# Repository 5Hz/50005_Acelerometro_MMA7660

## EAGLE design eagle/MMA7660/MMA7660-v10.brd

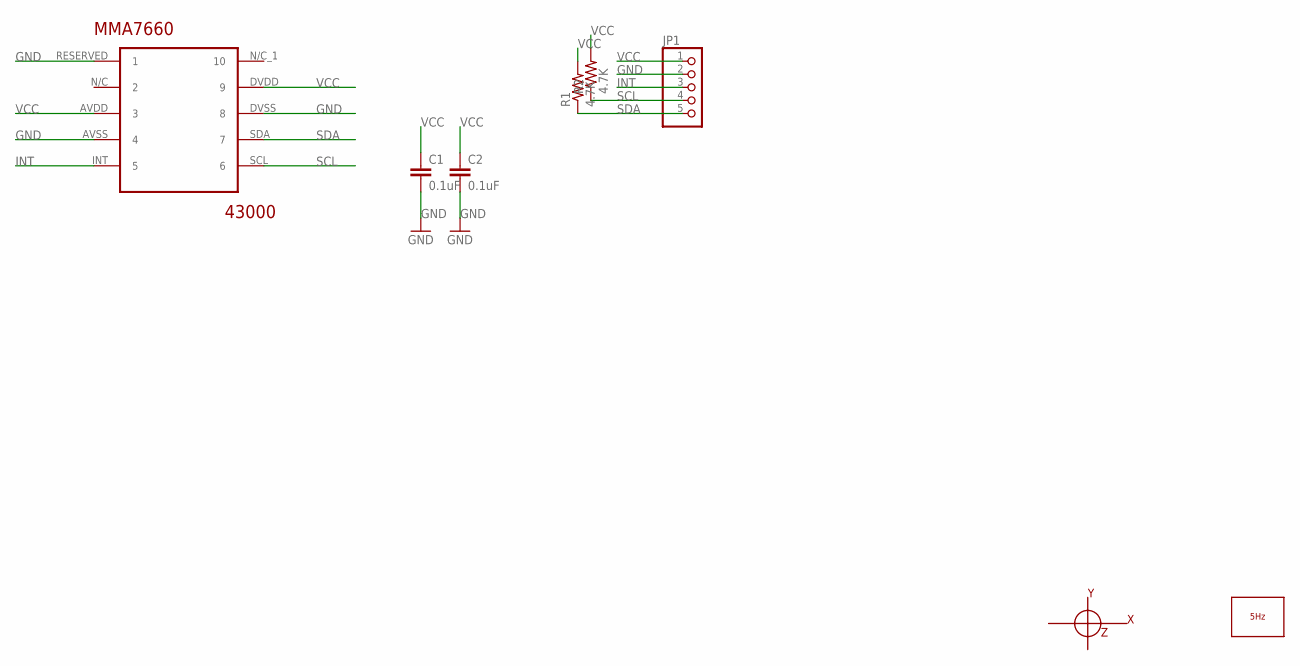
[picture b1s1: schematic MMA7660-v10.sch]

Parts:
C1, C2: 0.1uF; 0603-CAP
JP1: PINHD-1X5; 1X05
LOGO1: LOGO_5HZ_H_5MM; 5HZ_LOGO_H_5MM
MMA7660: 43000; MMA7660FC
R1, R2: 4.7K; 1/6W-RES
U$4: EJES_CARTESIANO_5MM; EJE_CARTESIANO_5MM

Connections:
GND: C1.2, C2.2, JP1.2, MMA7660.AVSS (4), MMA7660.DVSS (8), MMA7660.RESERVED (1)
INT: JP1.3, MMA7660.INT (5)
SCL: JP1.4, MMA7660.SCL (6), R2.1
SDA: JP1.5, MMA7660.SDA (7), R1.1
VCC: C1.1, C2.1, JP1.1, MMA7660.AVDD (3), MMA7660.DVDD (9), R1.2, R2.2

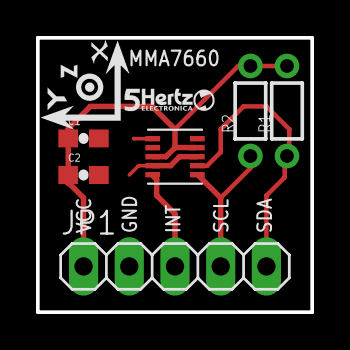
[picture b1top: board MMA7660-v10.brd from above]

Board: 2 copper layers, 15.2 x 15.2 mm, 8 parts (0 on the bottom side), 5 nets.

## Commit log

2014-01-09 creación
